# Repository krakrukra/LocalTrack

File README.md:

# LocalTrack  
  
#### Русская версия документации доступна [здесь](https://github.com/krakrukra/LocalTrack/blob/master/extra/wiki/rus/README.md)  
  
This device is an open source (both firmware and board level design) GPS data logger.  
You mount it with built-in magnets on some vehicle, flip the power switch and the location  
data is saved into internal flash storage. After some tracks were recorded, you can  
retrieve the device again and extract GPX track files via USB. You can then pass these  
files into mapping/analysis software of your choice, for example [viking](https://sourceforge.net/projects/viking), to get an  
easy to work with representation of recorded location data.  

This device is intended for use in applications where real-time tracking is not required,  
but other advantages of network-disconnected design are desirable, such as:  
  
1. No need to pay your cellular service provider.  
  
2. Local file storage, so you don't have to trust your data to some proprietary  
manufacturer's software or depend on a particular service being provided.  
  
3. Logger is harder to detect; if discovered, it is hard to trace where it came from,  
as it does not have information like IMEI, IMSI, payment history, etc. linked to it.  
  
4. Less power consumption and longer battery life.  
  
**CHECK THE [WIKI](https://github.com/krakrukra/LocalTrack/wiki) FOR HOW-TO-USE INFORMATION**  
  
---
  
## hardware
  
Project is designed using KiCad 6.0.11  
Check KiCad pcb file for PCB manufacturing info  
Check KiCad sch file + BOM.txt for component info  
  
Uses integrated full-speed (12Mbit/s) USB2.0 peripheral, with  
96MiB of available on-board flash memory for data storage;  
measured speeds for MSD access: read 800-850 KiB/s, write 700-750 KiB/s  
  
Fully assembled unit has dimensions of 85x55x32mm and weight of 175 grams.  
Hardware programmer device used in this project is [ST-Link V2](https://www.aliexpress.com/item/1823628996.html)  
  
SIM28 may come in several variants which have different USART speeds by default.  
Firmare here expects 9600 baudrate version. If you have different module version  
you will need to modify USART1 configuration in main.c and peripherals.c files.  
  
Device has a 3000mAh li-po battery and can function with battery voltage above 3V.  
If lower voltage is detected, device enters low battery mode and waits until  
the battery is recharged. Current consumption while tracking is around 40mA;  
while waiting in sleepmode (eg. due to lack of movement) it is less than 1mA.  
This results in about 70 hours of active tracking before battery is depleted.  
Battery can be charged via USB with up to 1A of current, so make sure to pick  
capable charging adapter and USB cable. Also, keep in mind that you will need  
a cable with extra long 8mm micro USB plug, instead of the usual 5.4mm plug.  
  
## firmware  
  
Programming language used = C  
Flashing software used = openocd 0.12.0  
IDE used = emacs text editor + Makefile  
  
The firmware was developed on debian 11.3 system, using gcc-arm-none-eabi  
toolchain (compiler, linker, binutils) and it does use gcc specific extentions.  
it was successfully compiled and tested with arm-none-eabi-gcc version 12.2.1  
  
Depends on libgcc.a, which is included in this repository. Linker script,  
startup code and openocd configuration files are included here as well.  
  
For easy in-field updates, you can use the DFU bootloader. There is a dfu  
firmware image available in **/firmware/firmware\_RRNNN.dfu** file. The name  
format is this: RR stands for board revision (13 = rev 1.3) , NNN stands  
for firmware version. For example, firmware\_13001.dfu means board  
revision 1.3, firmware version 1  

To automate firmware build process you can use make utility. If you  
open terminal in **/firmware/** directory, you could run these commands:  
  
> make  
> make upload  
> make dfu  
> make clean  
  
"make" will compile source code and create several files, among them  
is firmware.bin which contains firmware to flash. "make upload" will  
flash this file via St-Link V2 programmer. Make sure to connect the  
programmer to the board properly, before you plug it into PC and run the  
command. "make dfu" will create a DFU firmware image from firmware.bin  
which can be used later by DFU flashing software. "make clean" will  
delete all the compiled or temporary files created by previous commands.  
  
## directories info  
  
#### /firmware/ ------------- contains makefile, linker script, source files; this is a build directory  
/firmware/cmsis/ ------- header files from CMSIS compliant [STM32F0xx standard peripherals library](https://www.st.com/content/st_com/en/products/embedded-software/mcus-embedded-software/stm32-embedded-software/stm32-standard-peripheral-libraries/stsw-stm32048.html)  
/firmware/stdlib/ ---------- standard statically linked libraries (libgcc.a)  
/firmware/openocd/ ------- standard configuration files for openocd 0.12.0  
/firmware/fatfs/ ---------- [chan fatfs](http://www.elm-chan.org/fsw/ff/00index_e.html) filesystem module + W25N01GVZEIG disk driver  
/firmware/usb/ ------------ USB system and MSD class device implementation  
/firmware/main/ ------- main application files, interrupt vector table, IRQ handlers and startup code  
/firmware/dfuse-pack.py ------- python script to create .dfu firmware images  
/firmware/linkScript.ld ------- custom linker script for the GNU linker (ld)  
/firmware/Makefile ------- file used by GNU make utility for build automation  
/firmware/firmware_13NNN.dfu ------ pre-compiled firmware image in DfuSe format (STM32)  
  
#### /hardware/ ------------------- contains KiCad project, schematic, PCB files  
/hardware/LocalTrack.symbols/ ---- project specific symbol library  
/hardware/LocalTrack.pretty/ ----- project specific footprint library  
/hardware/gerbers/ ----------- gerber+excellon fabrication output files  
/hardware/BOM.txt --------- list of parts and accessories needed for DIY assembly  
  
#### /mechanical/ ------------------- contains device's mechanical information  
/mechanical/drawings/ ---- mechanical drawings for some of the parts  
/mechanical/KH-F20.FCStd --- freecad model for the plastic enclosure  
  
#### /extra/ -------------------  contains pictures, documentation, etc.  
/extra/photos/ ---------------- photos of the device  
/extra/wiki/ ------------------ github wiki pages  
  
## contact info  
  
if you have a problem / question / feature request, here are your options for contacting me:  
send me an email to krakrukra@tutanota.com  
create a new github issue (check [closed issues](https://github.com/krakrukra/LocalTrack/issues?q=is%3Aissue+is%3Aclosed) first)  
also, you can check out my [youtube channel](https://www.youtube.com/channel/UC8HZCV1vNmZvp7ci1vNmj7g)  
  
For extra security, you could use my PGP public key saved in [/extra/pubkey.asc](https://github.com/krakrukra/LocalTrack/blob/master/extra/pubkey.asc).

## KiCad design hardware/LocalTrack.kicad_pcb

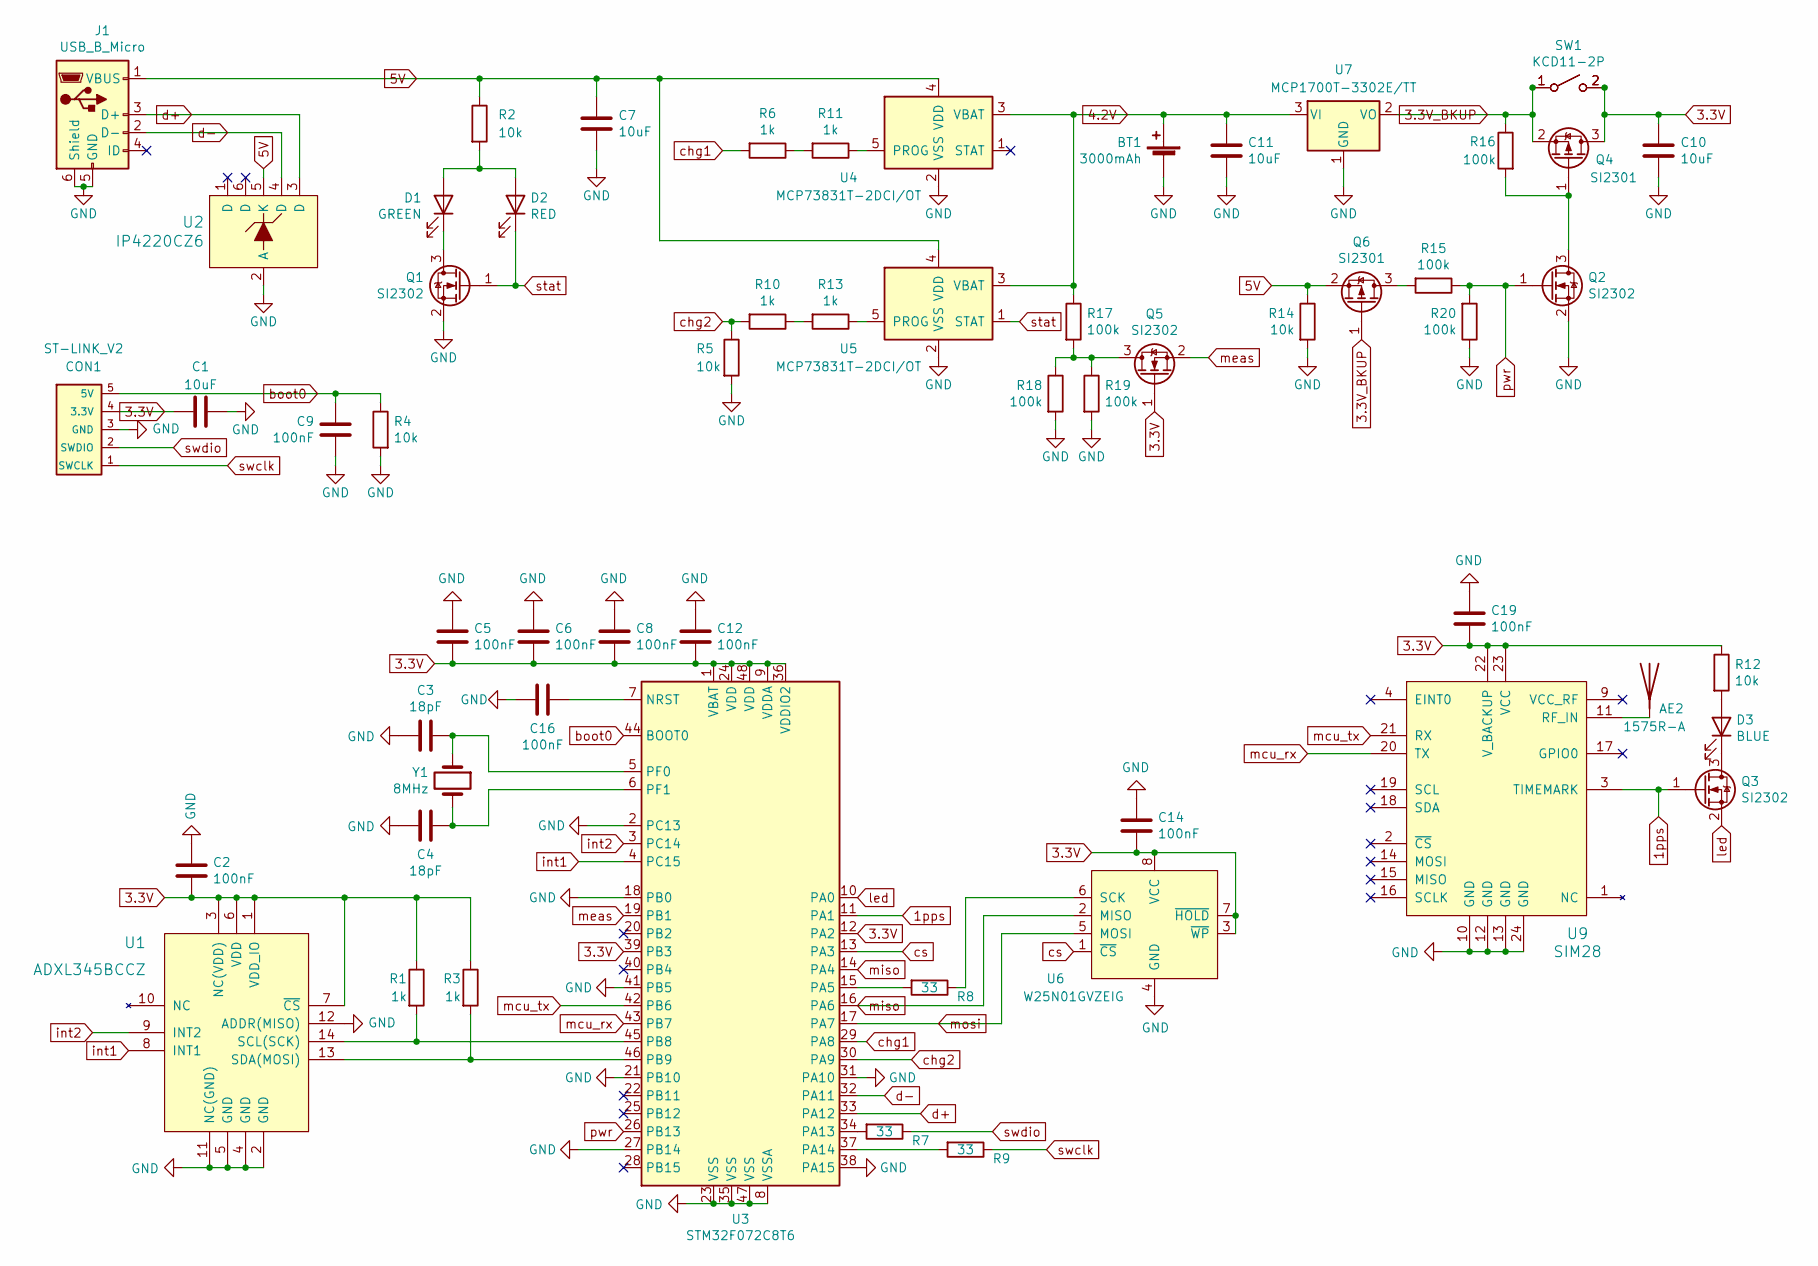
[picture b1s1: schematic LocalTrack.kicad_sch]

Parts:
AE2: 1575R-A
BT1: 3000mAh; JST_PH_B2B-PH-K_1x02_P2.00mm_Vertical
C1, C7, C10, C11: 10uF; C_0805_2012Metric
C2, C5, C6, C8, C9, C12, C14, C16, C19: 100nF; C_0603_1608Metric
C3, C4: 18pF; C_0603_1608Metric
CON1: ST-LINK_V2; PinHeader_1x05_P2.54mm_Vertical
D1: GREEN; LED_0603_1608Metric
D2: RED; LED_0603_1608Metric
D3: BLUE; LED_0603_1608Metric
J1: USB_B_Micro; MicroUSB_B
Q1, Q2, Q3, Q5: SI2302; SOT-23
Q4, Q6: SI2301; SOT-23
R1, R3, R6, R10, R11, R13: 1k; R_0603_1608Metric
R2, R4, R5, R12, R14: 10k; R_0603_1608Metric
R7, R8, R9: 33; R_0603_1608Metric
R15, R16, R17, R18, R19, R20: 100k; R_0603_1608Metric
SW1: KCD11-2P; KCD1-11
TP1: test pins; TestPins
U1: ADXL345BCCZ; LGA-14_3x5mm_P0.8mm_LayoutBorder1x6y
U2: IP4220CZ6; TSOP-6_1.65x3.05mm_P0.95mm
U3: STM32F072C8T6; LQFP-48_7x7mm_P0.5mm
U4, U5: MCP73831T-2DCI/OT; SOT-23-5
U6: W25N01GVZEIG; WSON-8_8x6mm
U7: MCP1700T-3302E/TT; SOT-23
U9: SIM28
Y1: 8MHz; Crystal_SMD_5032-2Pin_5.0x3.2mm

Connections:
1pps: Q3.1 (G), U3.11 (PA1), U9.3 (TIMEMARK)
3.3V: C1.1, C2.2, C5.2, C6.2, C8.2, C10.1, C12.2, C14.2, C19.2, CON1.4 (3.3V), Q4.3 (D), Q5.1 (G), R1.1, R3.1, R12.1, SW1.2 (B), TP1.2 (B), U1.1 (VDD_IO), U1.3 (NC(VDD)), U1.6 (VDD), U1.7 (~CS), U3.1 (VBAT), U3.9 (VDDA), U3.12 (PA2), U3.24 (VDD), U3.36 (VDDIO2), U3.39 (PB3), U3.48 (VDD), U6.3 (~WP), U6.7 (~HOLD), U6.8 (VCC), U9.22 (V_BACKUP), U9.23 (VCC)
3.3V_BKUP: Q4.2 (S), Q6.1 (G), R16.1, SW1.1 (A), TP1.1 (A), U7.2 (VO)
4.2V: BT1.1 (+), C11.1, R17.1, U4.3 (VBAT), U5.3 (VBAT), U7.3 (VI)
5V: C7.1, J1.1 (VBUS), Q6.2 (S), R2.1, R14.1, U2.5 (K), U4.4 (VDD), U5.4 (VDD)
GND: BT1.2 (-), C1.2, C2.1, C3.2, C4.2, C5.1, C6.1, C7.2, C8.1, C9.2, C10.2, C11.2, C12.1, C14.1, C16.2, C19.1, CON1.3 (GND), J1.5 (GND), J1.6 (Shield), Q1.2 (S), Q2.2 (S), R4.2, R5.2, R14.2, R18.2, R19.2, R20.1, U1.2 (GND), U1.4 (GND), U1.5 (GND), U1.11 (NC(GND)), U1.12 (ADDR(MISO)), U2.2 (A), U3.2 (PC13), U3.8 (VSSA), U3.18 (PB0), U3.21 (PB10), U3.23 (VSS), U3.27 (PB14), U3.31 (PA10), U3.35 (VSS), U3.38 (PA15), U3.41 (PB5), U3.47 (VSS), U4.2 (VSS), U5.2 (VSS), U6.4 (GND), U6.9 (GND), U7.1 (GND), U9.10 (GND), U9.12 (GND), U9.13 (GND), U9.24 (GND)
unnamed: AE2.1, U9.11 (RF_IN)
unnamed: C3.1, U3.5 (PF0), Y1.1
unnamed: C4.1, U3.6 (PF1), Y1.2
unnamed: C16.1, U3.7 (NRST)
unnamed: D1.1 (K), Q1.3 (D)
unnamed: D1.2 (A), D2.2 (A), R2.2
unnamed: D3.1 (K), Q3.3 (D)
unnamed: D3.2 (A), R12.2
unnamed: Q2.3 (D), Q4.1 (G), R16.2
unnamed: Q5.3 (D), R17.2, R18.1, R19.1
unnamed: Q6.3 (D), R15.2
unnamed: R1.2, U1.14 (SCL(SCK)), U3.45 (PB8)
unnamed: R3.2, U1.13 (SDA(MOSI)), U3.46 (PB9)
unnamed: R7.2, U3.34 (PA13)
unnamed: R8.1, U6.6 (SCK)
unnamed: R8.2, U3.15 (PA5)
unnamed: R9.2, U3.37 (PA14)
unnamed: R10.1, R13.2
unnamed: R11.1, U4.5 (PROG)
unnamed: R6.1, R11.2
unnamed: R13.1, U5.5 (PROG)
unnamed: U9.1 (NC), U9.5 (NC), U9.6 (NC), U9.7 (NC), U9.8 (NC)
boot0: C9.1, CON1.5 (5V), R4.1, U3.44 (BOOT0)
chg1: R6.2, U3.29 (PA8)
chg2: R5.1, R10.2, U3.30 (PA9)
cs: U3.13 (PA3), U6.1 (~CS)
d+: J1.3 (D+), U2.3 (D), U3.33 (PA12)
d-: J1.2 (D-), U2.4 (D), U3.32 (PA11)
int1: U1.8 (INT1), U3.4 (PC15)
int2: U1.9 (INT2), U3.3 (PC14)
led: Q3.2 (S), U3.10 (PA0)
mcu_rx: U3.43 (PB7), U9.20 (TX)
mcu_tx: U3.42 (PB6), U9.21 (RX)
meas: Q5.2 (S), U3.19 (PB1)
miso: U3.14 (PA4), U3.16 (PA6), U6.2 (MISO)
mosi: U3.17 (PA7), U6.5 (MOSI)
pwr: Q2.1 (G), R15.1, R20.2, U3.26 (PB13)
stat: D2.1 (K), Q1.1 (G), U5.1 (STAT)
swclk: CON1.1 (SWCLK), R9.1
swdio: CON1.2 (SWDIO), R7.1

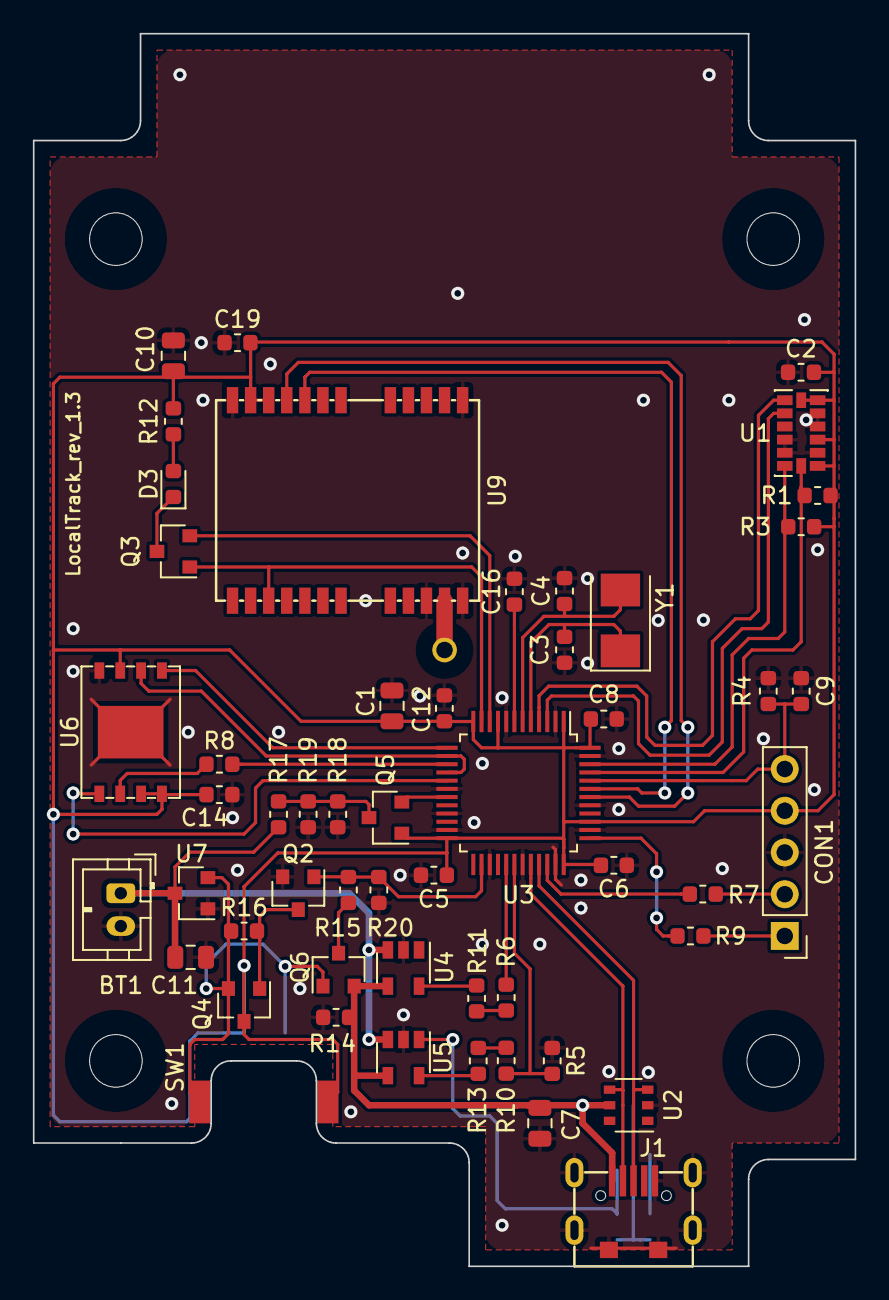
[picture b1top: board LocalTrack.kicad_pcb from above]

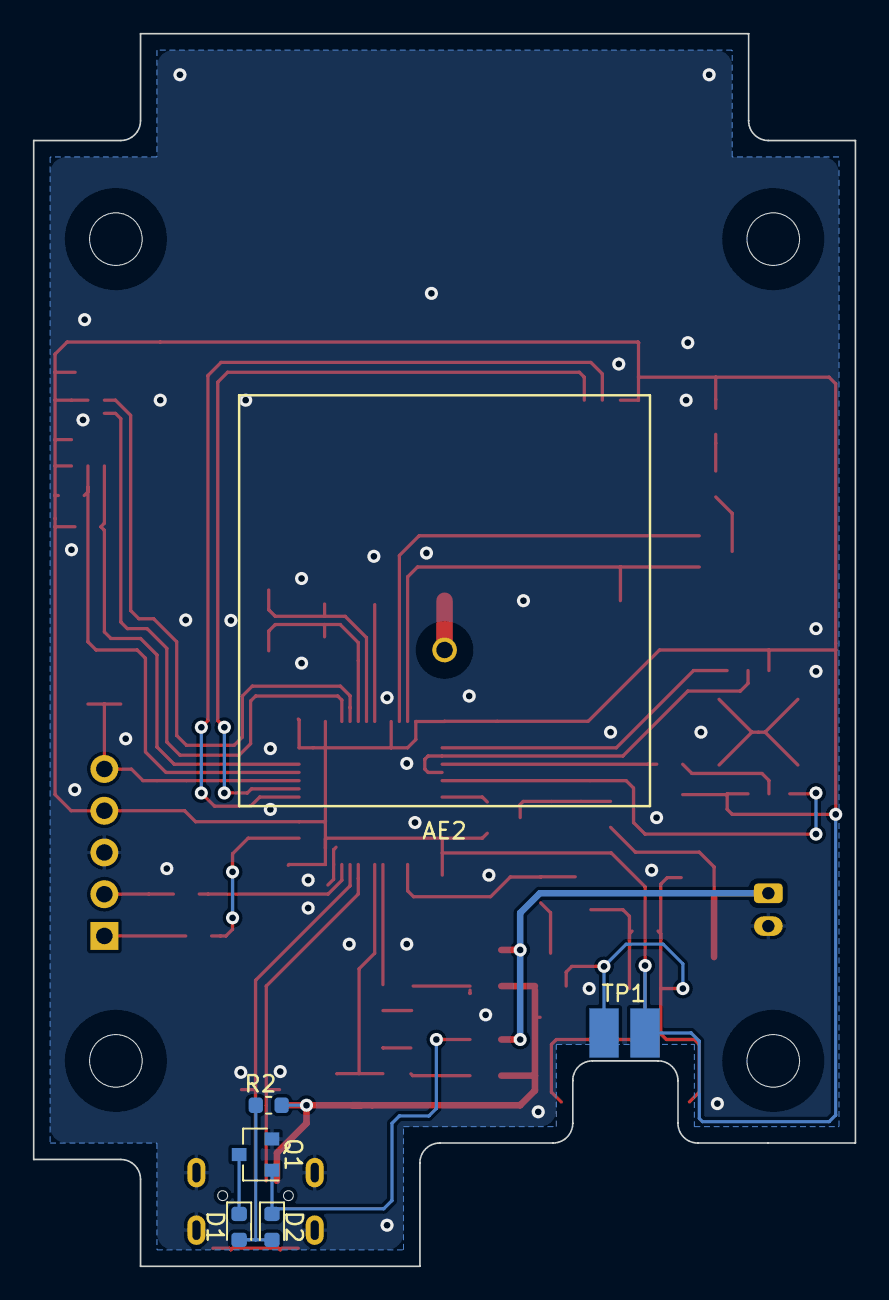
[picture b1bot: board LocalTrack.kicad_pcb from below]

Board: 2 copper layers, 50.0 x 75.0 mm, 59 parts (6 on the bottom side), 46 nets.

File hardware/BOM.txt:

LocalTrack_rev1.3 ----------------------- 28.10.2020 (dd.mm.yyyy)

electronic and mechanical parts are available on aliexpress / lcsc
example links to these items are for information purposes, check
for offers with better prices and shipping details yourself

quantities specified in this file are pieces per single PCB


STM32F072C8T6 microcontroller --- 1pcs
W25N01GVZEIG 128MiB flash memory chip --- 1pcs

SIM28 GPS receiver module --- 1pcs
1575R-A 25x25x4mm GPS patch antenna 1575.42MHz --- 1pcs

MCP1700T-3302E/TT 3.3V LDO voltage regulator --- 1pcs
MCP73831T-2DCI single li-po cell charge controller IC --- 2pcs
SI2302 N-channel mosfet --- 4pcs
SI2301 P-channel mosfet --- 2pcs
IP4220CZ6 ESD protection diode --- 1pcs
ADXL345BCCZ MEMS accelerometer --- 1pcs
0805 (metric 2012) ceramic capacitor 10uF X5R 10% 16V --- 4pcs
0603 (metric 1608) ceramic capacitor 100nF X7R 10% 50V --- 9pcs
0603 (metric 1608) ceramic capacitor 18pF C0G 5% 50V --- 2pcs
0603 (metric 1608) resistor 100 kOhm 5% tolerance --- 6pcs
0603 (metric 1608) resistor 10 kOhm 5% tolerance --- 5pcs
0603 (metric 1608) resistor 1 kOhm 5% tolerance --- 6pcs
0603 (metric 1608) resistor 33 Ohm 5% tolerance --- 3pcs
(metric 5032) NX5032GA 8MHz crystal resonator --- 1pcs
0603 (metric 1608) LED RED --- 1pcs
0603 (metric 1608) LED GREEN --- 1pcs
0603 (metric 1608) LED BLUE --- 1pcs


5x1 male pin header, vertical, 2.54mm pitch --- 1pcs

noname? horizontal micro USB connector --- 1pcs
    https://www.aliexpress.com/item/32765504799.html

8.4mm diameter, 3mm length (without head) rubber plug --- 1pcs
    https://www.aliexpress.com/item/32974255931.html

KCD1-11 rocker switch --- 1pcs
    I recommend to have a waterproof cover as provided via link below
    https://aliexpress.com/item/1005001835611654.html

EHAO 3.7V 3000mAh li-po battery 103565 --- 1pcs
    https://www.aliexpress.com/item/32879938149.html

cyllindrical neodymium magnet 20mm diameter, 3mm height --- 6pcs
    these are glued on to removable lid, battery is then glued on top of that
    https://www.aliexpress.com/item/1005001531120300.html

KH-F20 plastic enclosure (search aliexpress for 85x58x33mm enclosure), no mounting ears, nontransparent lid --- 1pcs
    https://www.aliexpress.com/item/32894036224.html

M3 countersunk head screw, 14mm length (without head) --- 4 pcs
    these should be included together with KH-F20 enclosure from the seller

M3 screw, 4mm length (without head) --- 4pcs
    https://www.aliexpress.com/item/32599502547.html

---------------------------------------------------------------------------------------------------

List of Accessories:

charging micro USB cable (1A or more) with extra long 8mm plug --- 1pcs
    https://www.aliexpress.com/item/32898415553.html

USB charger with detachable cable, output current of 1A or more --- 1pcs
    https://aliexpress.com/item/1005002034160981.html

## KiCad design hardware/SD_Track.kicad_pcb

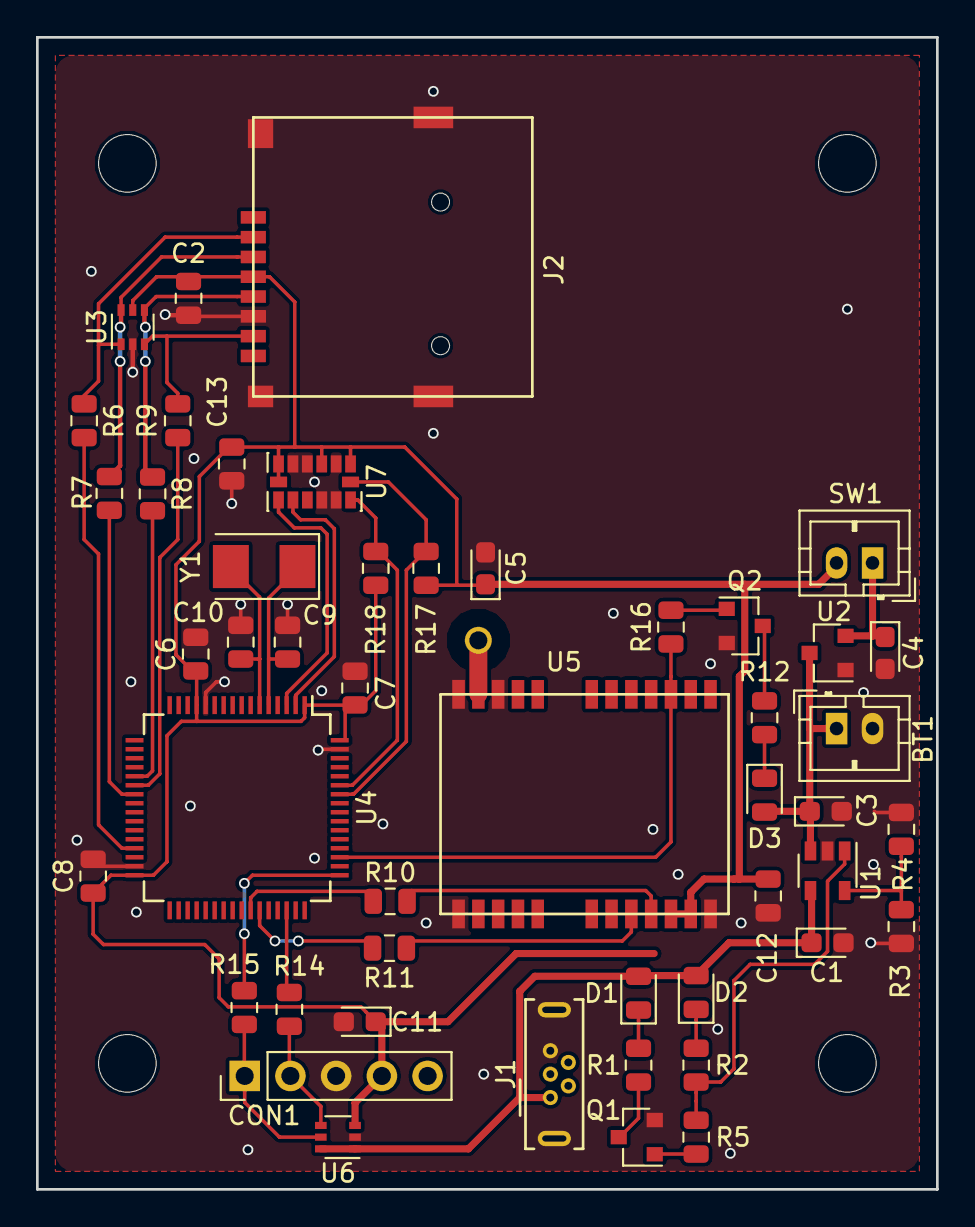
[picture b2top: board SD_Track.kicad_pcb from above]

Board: 2 copper layers, 50.0 x 64.0 mm, 49 parts (1 on the bottom side), 38 nets.

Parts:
AE1: 1575R-A
BT1: 3.7V 3000mah; JST_PH_B2B-PH-K_1x02_P2.00mm_Vertical
C1, C3, C4, C5, C11: 10uF; CP_EIA-2012-12_Kemet-R
C2, C6, C7, C8, C12, C13: 100nF; C_0805_2012Metric
C9, C10: 20pF; C_0805_2012Metric
CON1: ST-LINK_V2; PinHeader_1x05_P2.54mm_Vertical
D1: GREEN; LED_0805_2012Metric
D2: RED; LED_0805_2012Metric
D3: BLUE; LED_0805_2012Metric
J1: USB_B_Micro; USB_Micro-B_Wuerth_614105150721_Vertical
J2: TFP09-2-12B
Q1, Q2: MMBT3904; SOT-23
R1, R2, R3, R4, R5, R12, R16, R17, R18: 4.7k; R_0805_2012Metric
R6, R7, R8, R9, R10, R11, R14, R15: 33; R_0805_2012Metric
SW1: KCD11; JST_PH_B2B-PH-K_1x02_P2.00mm_Vertical
U1: MCP73831T-2DCI; SOT-23-5
U2: MCP1700T-3302E_SOT23; SOT-23
U3, U6: SMF05C; SOT-363_SC-70-6
U4: STM32F030R8Tx; LQFP-64_10x10mm_P0.5mm
U5: SIM28
U7: ADXL345; LGA-14_3x5mm_P0.8mm_LayoutBorder1x6y
Y1: 8MHz; Crystal_SMD_5032-2Pin_5.0x3.2mm

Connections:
3.3V: C2.1, C5.1, C6.1, C7.1, C8.1, C11.1, C12.1, C13.1, CON1.4, J2.4, R17.2, R18.2, SW1.2, U3.5, U4.1, U4.13, U4.32, U4.64, U5.22, U5.23, U6.3, U7.1, U7.3, U7.6, U7.7
4.2V: BT1.1, C3.1, D3.2, U1.3, U2.3
5V: C1.1, D1.2, D2.2, J1.1, U1.4, U6.1, U6.6
GND: BT1.2, C1.2, C2.2, C3.2, C4.2, C5.2, C6.2, C7.2, C8.2, C9.2, C10.2, C11.2, C12.2, C13.2, CON1.3, J1.5, J1.6, J2.6, J2.9, Q1.2, Q2.2, R3.1, R4.1, U1.2, U2.1, U3.2, U4.12, U4.31, U4.63, U5.10, U5.12, U5.13, U5.24, U6.2, U7.2, U7.4, U7.5, U7.11, U7.12
unnamed: AE1.1, U5.11
unnamed: C4.1, SW1.1, U2.2
unnamed: C9.1, U4.5, Y1.1
unnamed: C10.1, U4.6, Y1.2
unnamed: D1.1, R1.2
unnamed: D2.1, R2.2
unnamed: D3.1, R12.2
unnamed: J2.2, R6.1, U3.1
unnamed: J2.3, R7.1, U3.6
unnamed: J2.5, R8.1, U3.4
unnamed: J2.7, R9.1, U3.3
unnamed: Q1.1, R5.1
unnamed: Q1.3, R1.1
unnamed: Q2.1, R16.2
unnamed: Q2.3, R12.1
unnamed: R3.2, R4.2, U1.5
unnamed: R10.2, U4.42
unnamed: R11.2, U4.43
unnamed: R14.2, U4.46
unnamed: R15.2, U4.49
unnamed: U4.2, U7.9
unnamed: U4.3, U7.8
charge_stat: R2.1, R5.2, U1.1
ledstat: R16.1, U4.51, U5.3
miso: R9.2, U4.22
mosi: R7.2, U4.23
sck: R8.2, U4.21
scl: R17.1, U4.58, U7.14
sda: R18.1, U4.59, U7.13
sim28_rx: R10.1, U5.21
sim28_tx: R11.1, U5.20
ss: R6.2, U4.29
swclk: CON1.1, R15.1, U6.5
swdio: CON1.2, R14.1, U6.4

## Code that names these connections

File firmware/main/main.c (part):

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  SCB->SCR |= (1<<2);//set stop mode as default low power mode
  
  //ports configuration
  GPIOB->MODER |= (1<<19)|(1<<17)|(1<<15)|(1<<13)|(1<<3)|(1<<2);//PB6, PB7, PB8, PB9 are in alternate function mode, PB1 is analog input
  GPIOB->AFR[1] |= (1<<4)|(1<<0);//PB8, PB9 are I2C1; PB6, PB7 are USART1
  SYSCFG->CFGR1 |= (1<<10)|(1<<9);//remap USART1 DMA requests to channels 4 and 5
  
  //EXTI configuration
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      while(GPIOB->IDR & (1<<13)) usb_handler();//while USB cable is plugged in, act as flash disk only
      
      //once USB cable was disconnected, decrease current draw to 83mA, disable USB peripheral
      GPIOA->MODER &= ~((1<<18)|(1<<16));//disconnect chg1 and chg2 lines from ground
      RCC->APB1RSTR |=  (1<<23);//reset USB peripheral
      
      RCC->CFGR = (1<<20)|(1<<16)|(1<<0);//set HSE as system clock
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
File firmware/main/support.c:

#include "../cmsis/stm32f0xx.h"

extern int main();
extern void dma_handler() __attribute__((interrupt));

static void startup();
static inline void initialize_data(unsigned int* from, unsigned int* data_start, unsigned int* data_end) __attribute__((always_inline));
static inline void initialize_bss(unsigned int* bss_start, unsigned int* bss_end) __attribute__((always_inline));

static void default_handler() __attribute__((interrupt));
static void rtc_handler() __attribute__((interrupt));
static void exti4_15() __attribute__((interrupt));

//these symbols are declared in the linker script
extern unsigned int __data_start__;//start of .data section in RAM
extern unsigned int __data_end__;//end of .data section in RAM
extern unsigned int __bss_end__;//end of .bss section in RAM
extern unsigned int __text_end__;//end of .text section in ROM

void* vectorTable[48] __attribute__(( section(".vectab,\"a\",%progbits@") )) =
  {
    (void*)0x20003FFC,//initial main SP value (16kB RAM size)
    (void*)&startup,//reset vector
    (void*)&default_handler,//NMI
    (void*)&default_handler,//HardFault
    (void*)0x00000000,//reserved
    (void*)0x00000000,//reserved
    (void*)0x00000000,//reserved
    (void*)0x00000000,//reserved
    (void*)0x00000000,//reserved
    (void*)0x00000000,//reserved
    (void*)0x00000000,//reserved
    (void*)&default_handler,//SVCall
    (void*)0x00000000,//reserved
    (void*)0x00000000,//reserved
    (void*)&default_handler,//PendSV
    (void*)&default_handler,//SysTick
    (void*)0x00000000,//IRQ0
    (void*)0x00000000,//IRQ1
    (void*)&rtc_handler,//IRQ2
    (void*)0x00000000,//IRQ3
    (void*)0x00000000,//IRQ4
    (void*)0x00000000,//IRQ5
    (void*)0x00000000,//IRQ6
    (void*)&exti4_15,//IRQ7
    (void*)0x00000000,//IRQ8
    (void*)0x00000000,//IRQ9
    (void*)&dma_handler,//IRQ10
    (void*)0x00000000,//IRQ11
    (void*)0x00000000,//IRQ12
    (void*)0x00000000,//IRQ13
    (void*)0x00000000,//IRQ14
    (void*)0x00000000,//IRQ15
    (void*)0x00000000,//IRQ16
    (void*)0x00000000,//IRQ17
    (void*)0x00000000,//IRQ18
    (void*)0x00000000,//IRQ19
    (void*)0x00000000,//IRQ20
    (void*)0x00000000,//IRQ21
    (void*)0x00000000,//IRQ22
    (void*)0x00000000,//IRQ23
    (void*)0x00000000,//IRQ24
    (void*)0x00000000,//IRQ25
    (void*)0x00000000,//IRQ26
    (void*)0x00000000,//IRQ27
    (void*)0x00000000,//IRQ28
    (void*)0x00000000,//IRQ29
    (void*)0x00000000,//IRQ30
    (void*)0x00000000 //IRQ31
  };

//copies initialized static variable values from ROM to RAM
static inline void initialize_data(unsigned int* from, unsigned int* data_start, unsigned int* data_end)
{
  while(data_start < data_end)
    {
      *data_start = *from;
      data_start++;
      from++;
    }
}

//writes to zero uninitialized static variable values in RAM
static inline void initialize_bss(unsigned int* bss_start, unsigned int* bss_end)
{
  while(bss_start < bss_end)
    {
      *bss_start = 0x00000000U;
      bss_start++;
    }
}

//the very first function that the CPU will run
static void startup()
{
  RCC->AHBENR |= (1<<17);//enable GPIOA clock
  GPIOA->MODER |= (1<<15)|(1<<13)|(1<<11)|(1<<6);//PA5, PA6, PA7 are in alternate function mode (SPI1); PA3 is output
  GPIOA->BSRR = (1<<3);//pull PA3 high (SPI1 CS output)
  
  RCC->CR |= (1<<19)|(1<<16);//enable HSE clock, clock security system
  
  initialize_data(&__text_end__, &__data_start__, &__data_end__);
  initialize_bss(&__data_end__, &__bss_end__);
  
  while( !(RCC->CR & (1<<17)) );//wait until HSE is ready
  RCC->CFGR = (1<<0);//set HSE as system clock
  while( !((RCC->CFGR & 0x0F) == 0b0101) );//wait until HSE is used as system clock
  RCC->CR &= ~(1<<0);//disable HSI clock
  
  main();
  
  NVIC_SystemReset();//if main() ever returns reset MCU
  return;
}

//default IRQ handler initiates system reset
static void default_handler()
{
  NVIC_SystemReset();
  return;
}

//EXTI 20 interrupt is only used to wake up from stop mode
static void rtc_handler()
{
  EXTI->PR = (1<<20);//clear EXTI line 20 interrupt flag
  return;
}

//EXTI line 15 interrupt is only used to wake up from stop mode
static void exti4_15()
{
  EXTI->PR = (1<<15);//clear EXTI line 15 interrupt flag
  return;
}

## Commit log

2020-10-30 new version release
2020-10-30 documentation update
2020-10-31 readme update
2021-01-29 removed extra TVS diode
2023-11-14 update to newer toolchain version
2024-02-02 status file update
2024-02-02 documentation fix
